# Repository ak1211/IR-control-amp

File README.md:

# IR-control-amp

## Overview
Infra Red remote control amplifier firmware on atmega328p

## Description
このソフトウエアはatmega328p使用  
赤外線リモコンコントロールヘッドホンアンプ基板Rev: A2.x用  
組込みファームウエアです。

## Requirements
Atmel Studio 7 (Version: 7.0.594 - )
© 2015 Atmel Corp.
All rights reserved.

## Compile and Link
Atmel Studio 7で[solution file](https://github.com/ak1211/IR-control-amp/blob/master/AudioAmpApplication/AudioAmpApplication.atsln)
を開いてコンパイル＆リンクを行ってください。

## License
[MIT](https://github.com/ak1211/IR-control-amp/blob/master/LICENSE)

## Author
[ak1211](https://github.com/ak1211/) - [blog](https://ak1211.com/index.php)

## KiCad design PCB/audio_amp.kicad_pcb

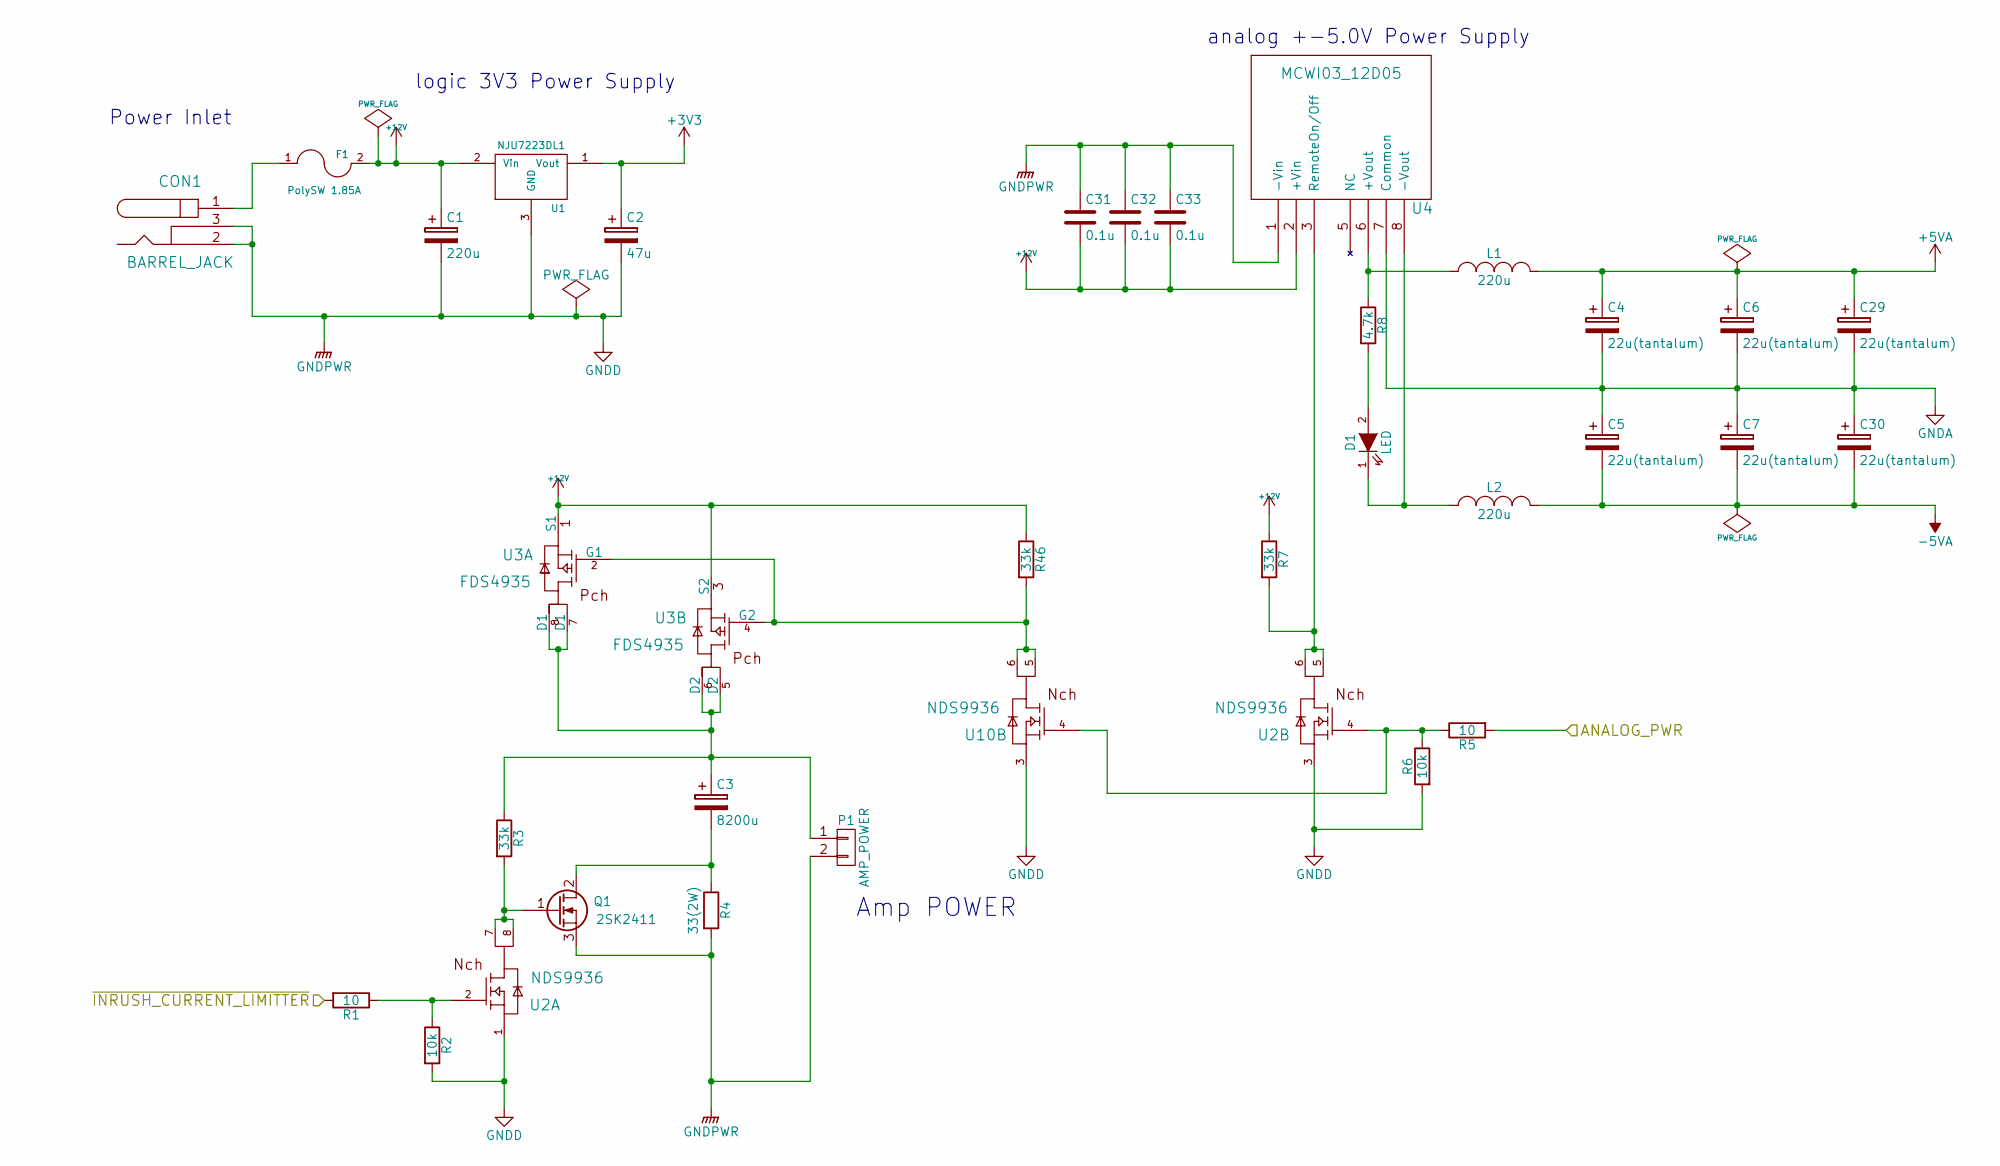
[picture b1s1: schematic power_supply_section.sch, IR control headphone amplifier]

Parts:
C1: 220u; c_elec_10x10.5
C2: 47u; c_elec_10x10.5
C3: 8200u; C_Radial_D18_L36_P7.5
C4, C5, C6, C7, C29, C30: 22u(tantalum); TantalC_SizeA_EIA-3216_HandSoldering
C31, C32, C33: 0.1u; C_0805_HandSoldering
CON1: BARREL_JACK
D1: LED; LED-0805
F1: PolySW 1.85A; Fuse_TE5_Littlefuse-395Series
L1, L2: 220u; Choke_SMD_10.4x10.4_H4.8
P1: AMP_POWER; Socket_MOLEX-KK-RM3-96mm_Lock_2pin_straight
Q1: 2SK2411; sot404
R1, R5: 10; R_0805_HandSoldering
R2, R6: 10k; R_0805_HandSoldering
R3, R7, R46: 33k; R_0805_HandSoldering
R4: 33(2W); Resistor_Horizontal_RM20mm
R8: 4.7k; R_0805_HandSoldering
U1: NJU7223DL1; sot428
U2, U10: NDS9936; SOIC-8_3.9x4.9mm_Pitch1.27mm
U3: FDS4935; SOIC-8_3.9x4.9mm_Pitch1.27mm
U4: MCWI03_12D05; MINMAX_MCWI03-12x

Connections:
+3V3: C2.1, U1.1 (Vout); also elsewhere on the board
+5VA: C4.1, C6.1, C29.1, L1.2; also elsewhere on the board
+12V: C1.1, C31.2, C32.2, C33.2, F1.2, R7.1, R46.1, U1.2 (Vin), U3.1 (S1), U3.3 (S2), U4.2 (+Vin); also elsewhere on the board
-5VA: C5.2, C7.2, C30.2, L2.2; also elsewhere on the board
/controller_section/ANALOG_PWR: R5.2; also elsewhere on the board
/controller_section/~INRUSH_CURRENT_LIMITTER: R1.2; also elsewhere on the board
GNDA: C4.2, C5.1, C6.2, C7.1, C29.2, C30.1, U4.7 (Common); also elsewhere on the board
GNDD: C1.2, C2.2, C31.1, C32.1, C33.1, CON1.2, CON1.3, P1.2, Q1.3 (S), R2.2, R4.2, R6.2, U1.3 (GND), U2.1, U2.3, U4.1 (-Vin), U10.3; also elsewhere on the board
unnamed: C3.1, P1.1, R3.1, U3.5 (D2), U3.6 (D2), U3.7 (D1), U3.8 (D1)
unnamed: C3.2, Q1.2 (D), R4.1
unnamed: CON1.1, F1.1
unnamed: D1.1 (K), L2.1, U4.8 (-Vout)
unnamed: D1.2 (A), R8.2
unnamed: L1.1, R8.1, U4.6 (+Vout)
unnamed: Q1.1 (G), R3.2, U2.7, U2.8
unnamed: R1.1, R2.1, U2.2
unnamed: R5.1, R6.1, U2.4, U10.4
unnamed: R7.2, U2.5, U2.6, U4.3 (RemoteOn/Off)
unnamed: R46.2, U3.2 (G1), U3.4 (G2), U10.5, U10.6

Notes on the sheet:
analog +-5.0V Power Supply
Power Inlet
logic 3V3 Power Supply
Amp POWER

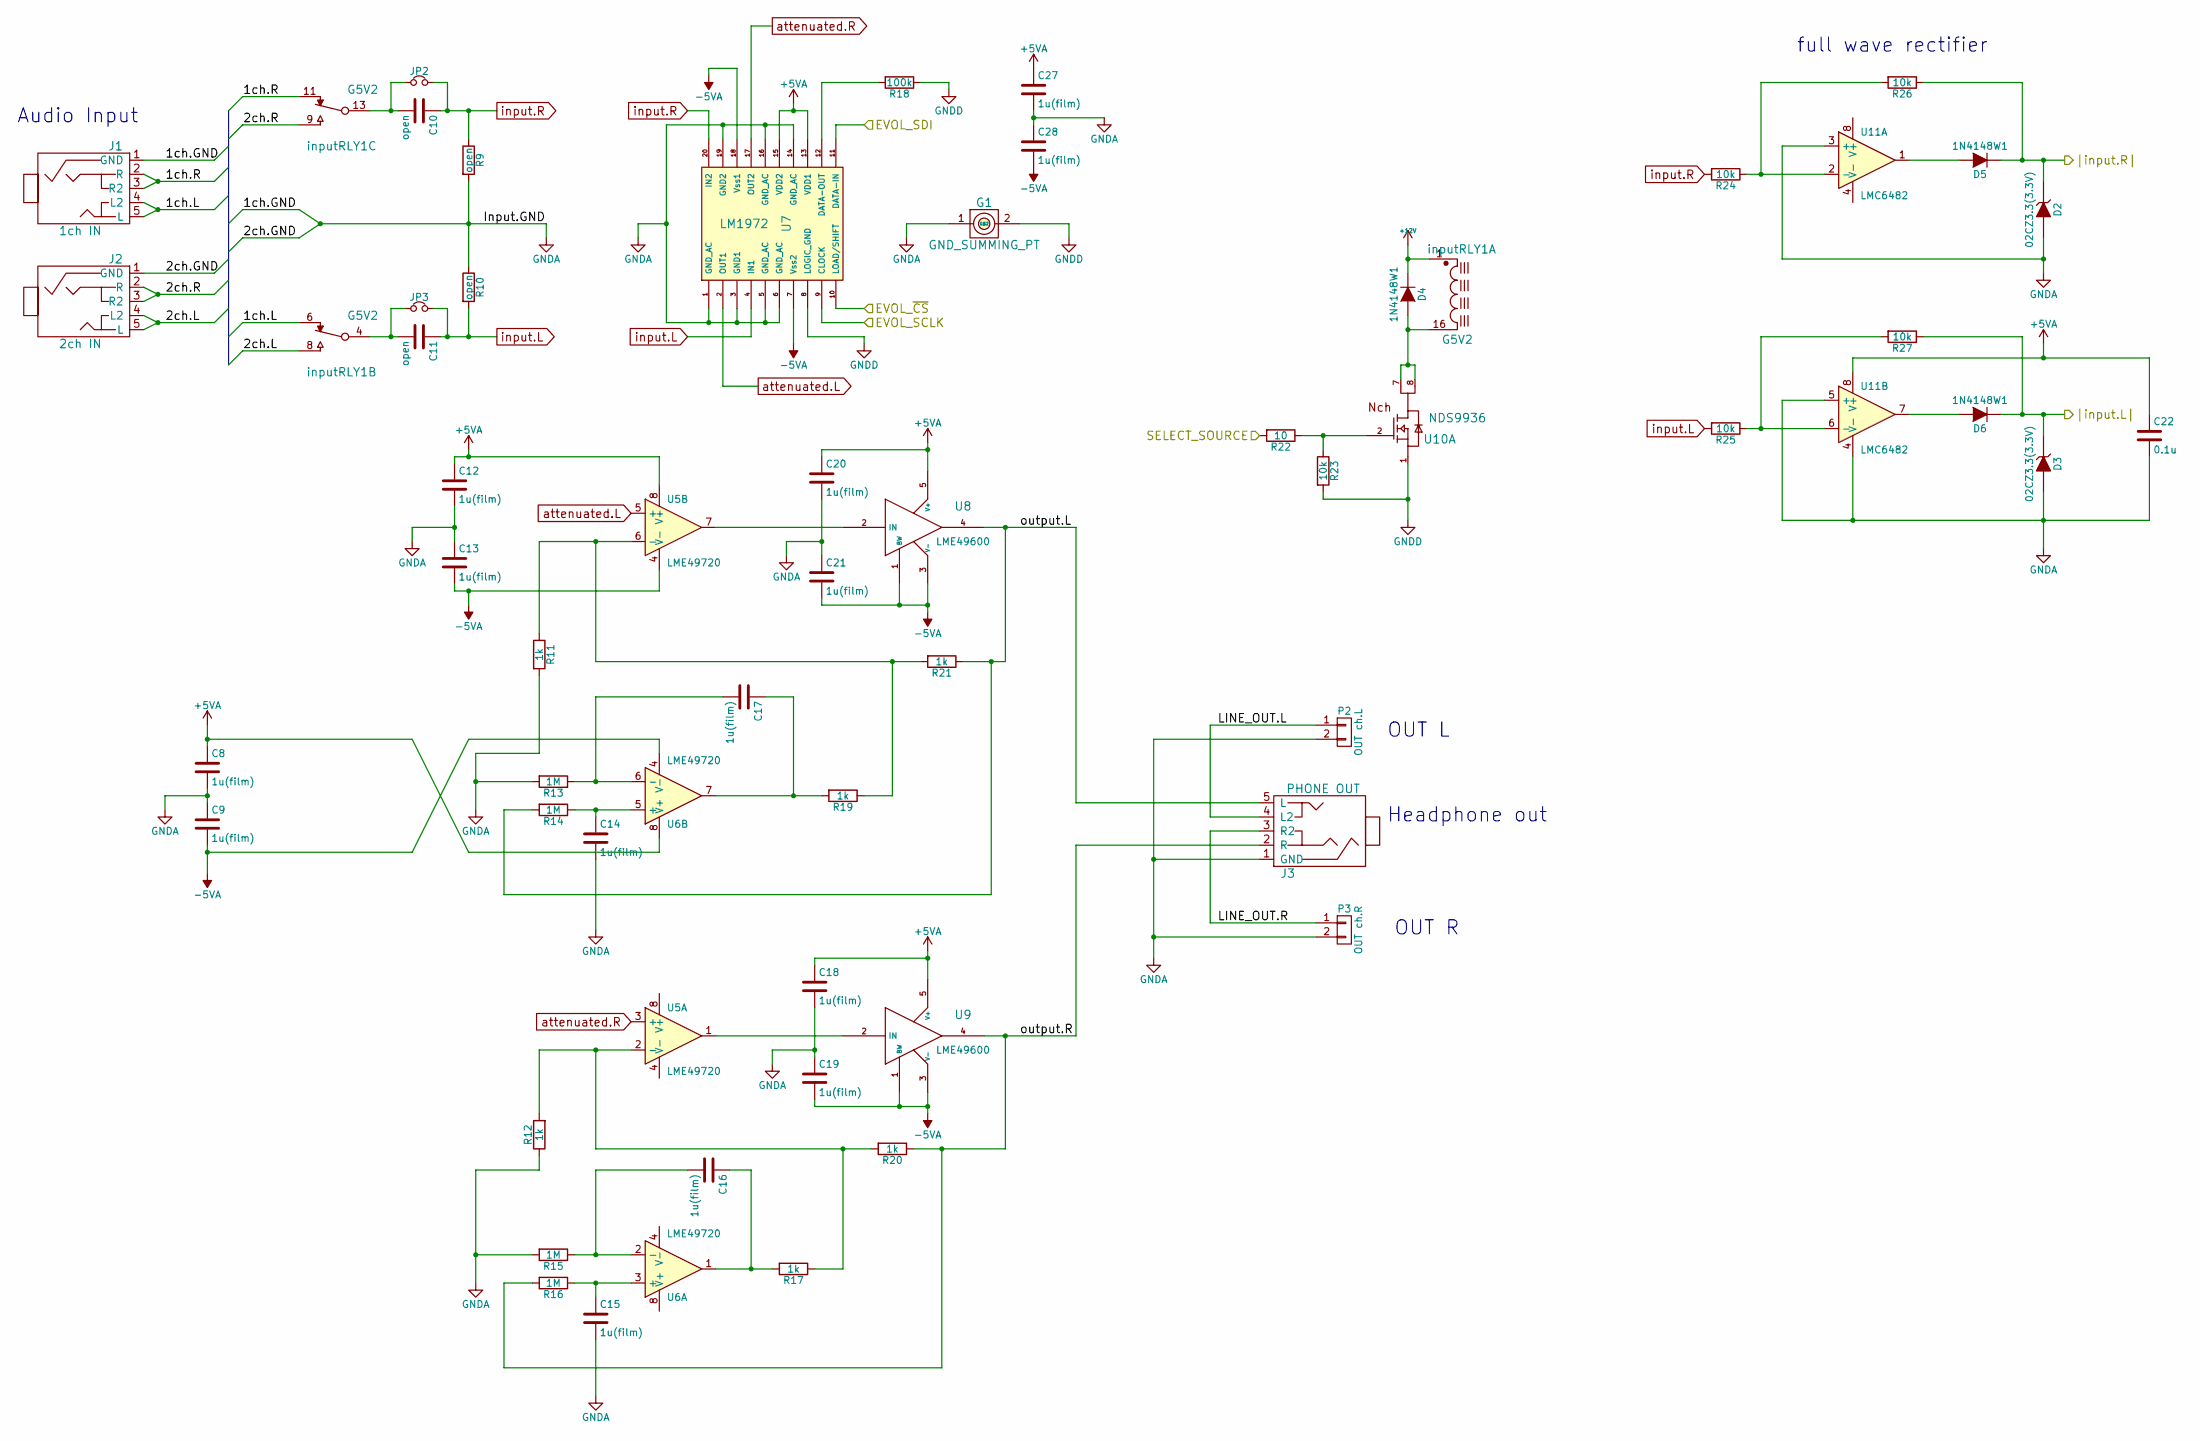
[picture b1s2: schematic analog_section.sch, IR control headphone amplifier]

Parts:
C8, C9, C12, C13, C14, C15, C16, C17, C18, C19, C20, C21, C27, C28: 1u(film); C_1206_HandSoldering
C10, C11: open; C_1206_HandSoldering
C22: 0.1u; C_0805_HandSoldering
D2, D3: 02CZ3.3(3.3V); SC-59
D4, D5, D6: 1N4148W1; SOD-123
G1: GND_SUMMING_PT
J1: 1ch IN; AJ-1780
J2: 2ch IN; AJ-1780
J3: PHONE OUT; AJ-1780
JP2, JP3: Jumper_NC_Small; GS2
P2: OUT ch.L; Socket_MOLEX-KK-RM2-54mm_Lock_2pin_straight
P3: OUT ch.R; Socket_MOLEX-KK-RM2-54mm_Lock_2pin_straight
R9, R10: open; R_0805_HandSoldering
R11, R12, R17, R19, R20, R21: 1k; R_0805_HandSoldering
R13, R14, R15, R16: 1M; R_0805_HandSoldering
R18: 100k; R_0805_HandSoldering
R22: 10; R_0805_HandSoldering
R23, R24, R25, R26, R27: 10k; R_0805_HandSoldering
U5, U6: LME49720
U7: LM1972; SOIC-20_7.5x12.8mm_Pitch1.27mm
U8, U9: LME49600
U10: NDS9936; SOIC-8_3.9x4.9mm_Pitch1.27mm
U11: LMC6482
inputRLY1: G5V2; G5V-2

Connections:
+5VA: C8.1, C12.1, C18.1, C20.1, C22.1, C27.1, U5.8 (V+), U6.8 (V+), U7.13 (VDD1), U7.15 (VDD2), U8.5 (V+), U9.5 (V+), U11.8 (V+); also elsewhere on the board
+12V: D4.1 (K), inputRLY1.1; also elsewhere on the board
-5VA: C9.2, C13.2, C19.2, C21.2, C28.2, U5.4 (V-), U6.4 (V-), U7.7 (Vss2), U7.18 (Vss1), U8.1 (BW), U8.3 (V-), U9.1 (BW), U9.3 (V-); also elsewhere on the board
/analog_section/1ch.L: J1.4 (L2), J1.5 (L), inputRLY1.6
/analog_section/1ch.R: J1.2 (R), J1.3 (R2), inputRLY1.11
/analog_section/2ch.L: J2.4 (L2), J2.5 (L), inputRLY1.8
/analog_section/2ch.R: J2.2 (R), J2.3 (R2), inputRLY1.9
/analog_section/EVOL_SCLK: U7.9 (CLOCK); also elsewhere on the board
/analog_section/EVOL_SDI: U7.11 (DATA-IN); also elsewhere on the board
/analog_section/EVOL_~CS: U7.10 (LOAD/SHIFT); also elsewhere on the board
/analog_section/LINE_OUT.L: J3.4 (L2), P2.1
/analog_section/LINE_OUT.R: J3.3 (R2), P3.1
/analog_section/SELECT_SOURCE: R22.2; also elsewhere on the board
/analog_section/output.L: J3.5 (L), R14.2, R21.1, U8.4
/analog_section/output.R: J3.2 (R), R16.2, R20.1, U9.4
/analog_section/|input.L|: D3.1 (K), D6.1 (K), R27.1; also elsewhere on the board
/analog_section/|input.R|: D2.1 (K), D5.1 (K), R26.1; also elsewhere on the board
GNDA: C8.2, C9.1, C12.2, C13.1, C14.2, C15.2, C18.2, C19.1, C20.2, C21.1, C22.2, C27.2, C28.1, D2.2 (A), D3.2 (A), G1.1 (G1), J1.1 (GND), J2.1 (GND), J3.1 (GND), P2.2, P3.2, R9.2, R10.1, R11.2, R12.1, R13.2, R15.2, U7.1 (GND_AC), U7.3 (GND1), U7.5 (GND_AC), U7.6 (GND_AC), U7.14 (GND_AC), U7.16 (GND_AC), U7.19 (GND2), U11.3 (+), U11.4 (V-), U11.5 (+); also elsewhere on the board
GNDD: G1.2 (G2), R18.1, R23.2, U7.8 (LOGIC_GND), U10.1; also elsewhere on the board
unnamed: C10.2, JP2.1, inputRLY1.13
unnamed: C11.2, JP3.1, inputRLY1.4
unnamed: C14.1, R14.1, U6.5 (+)
unnamed: C15.1, R16.1, U6.3 (+)
unnamed: C16.1, R17.2, U6.1
unnamed: C16.2, R15.1, U6.2 (-)
unnamed: C17.1, R19.2, U6.7
unnamed: C17.2, R13.1, U6.6 (-)
unnamed: D4.2 (A), U10.7, U10.8, inputRLY1.16
unnamed: D5.2 (A), U11.1
unnamed: D6.2 (A), U11.7
unnamed: R11.1, R19.1, R21.2, U5.6 (-)
unnamed: R12.2, R17.1, R20.2, U5.2 (-)
unnamed: R18.2, U7.12 (DATA-OUT)
unnamed: R22.1, R23.1, U10.2
unnamed: R24.1, R26.2, U11.2 (-)
unnamed: R25.1, R27.2, U11.6 (-)
unnamed: U5.1, U9.2 (IN)
unnamed: U5.7, U8.2 (IN)
attenuated.L: U5.5 (+), U7.2 (OUT1)
attenuated.R: U5.3 (+), U7.17 (OUT2)
input.L: C11.1, JP3.2, R10.2, R25.2, U7.4 (IN1)
input.R: C10.1, JP2.2, R9.1, R24.2, U7.20 (IN2)

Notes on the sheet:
OUT R
Audio Input
Headphone out
full wave rectifier
OUT L

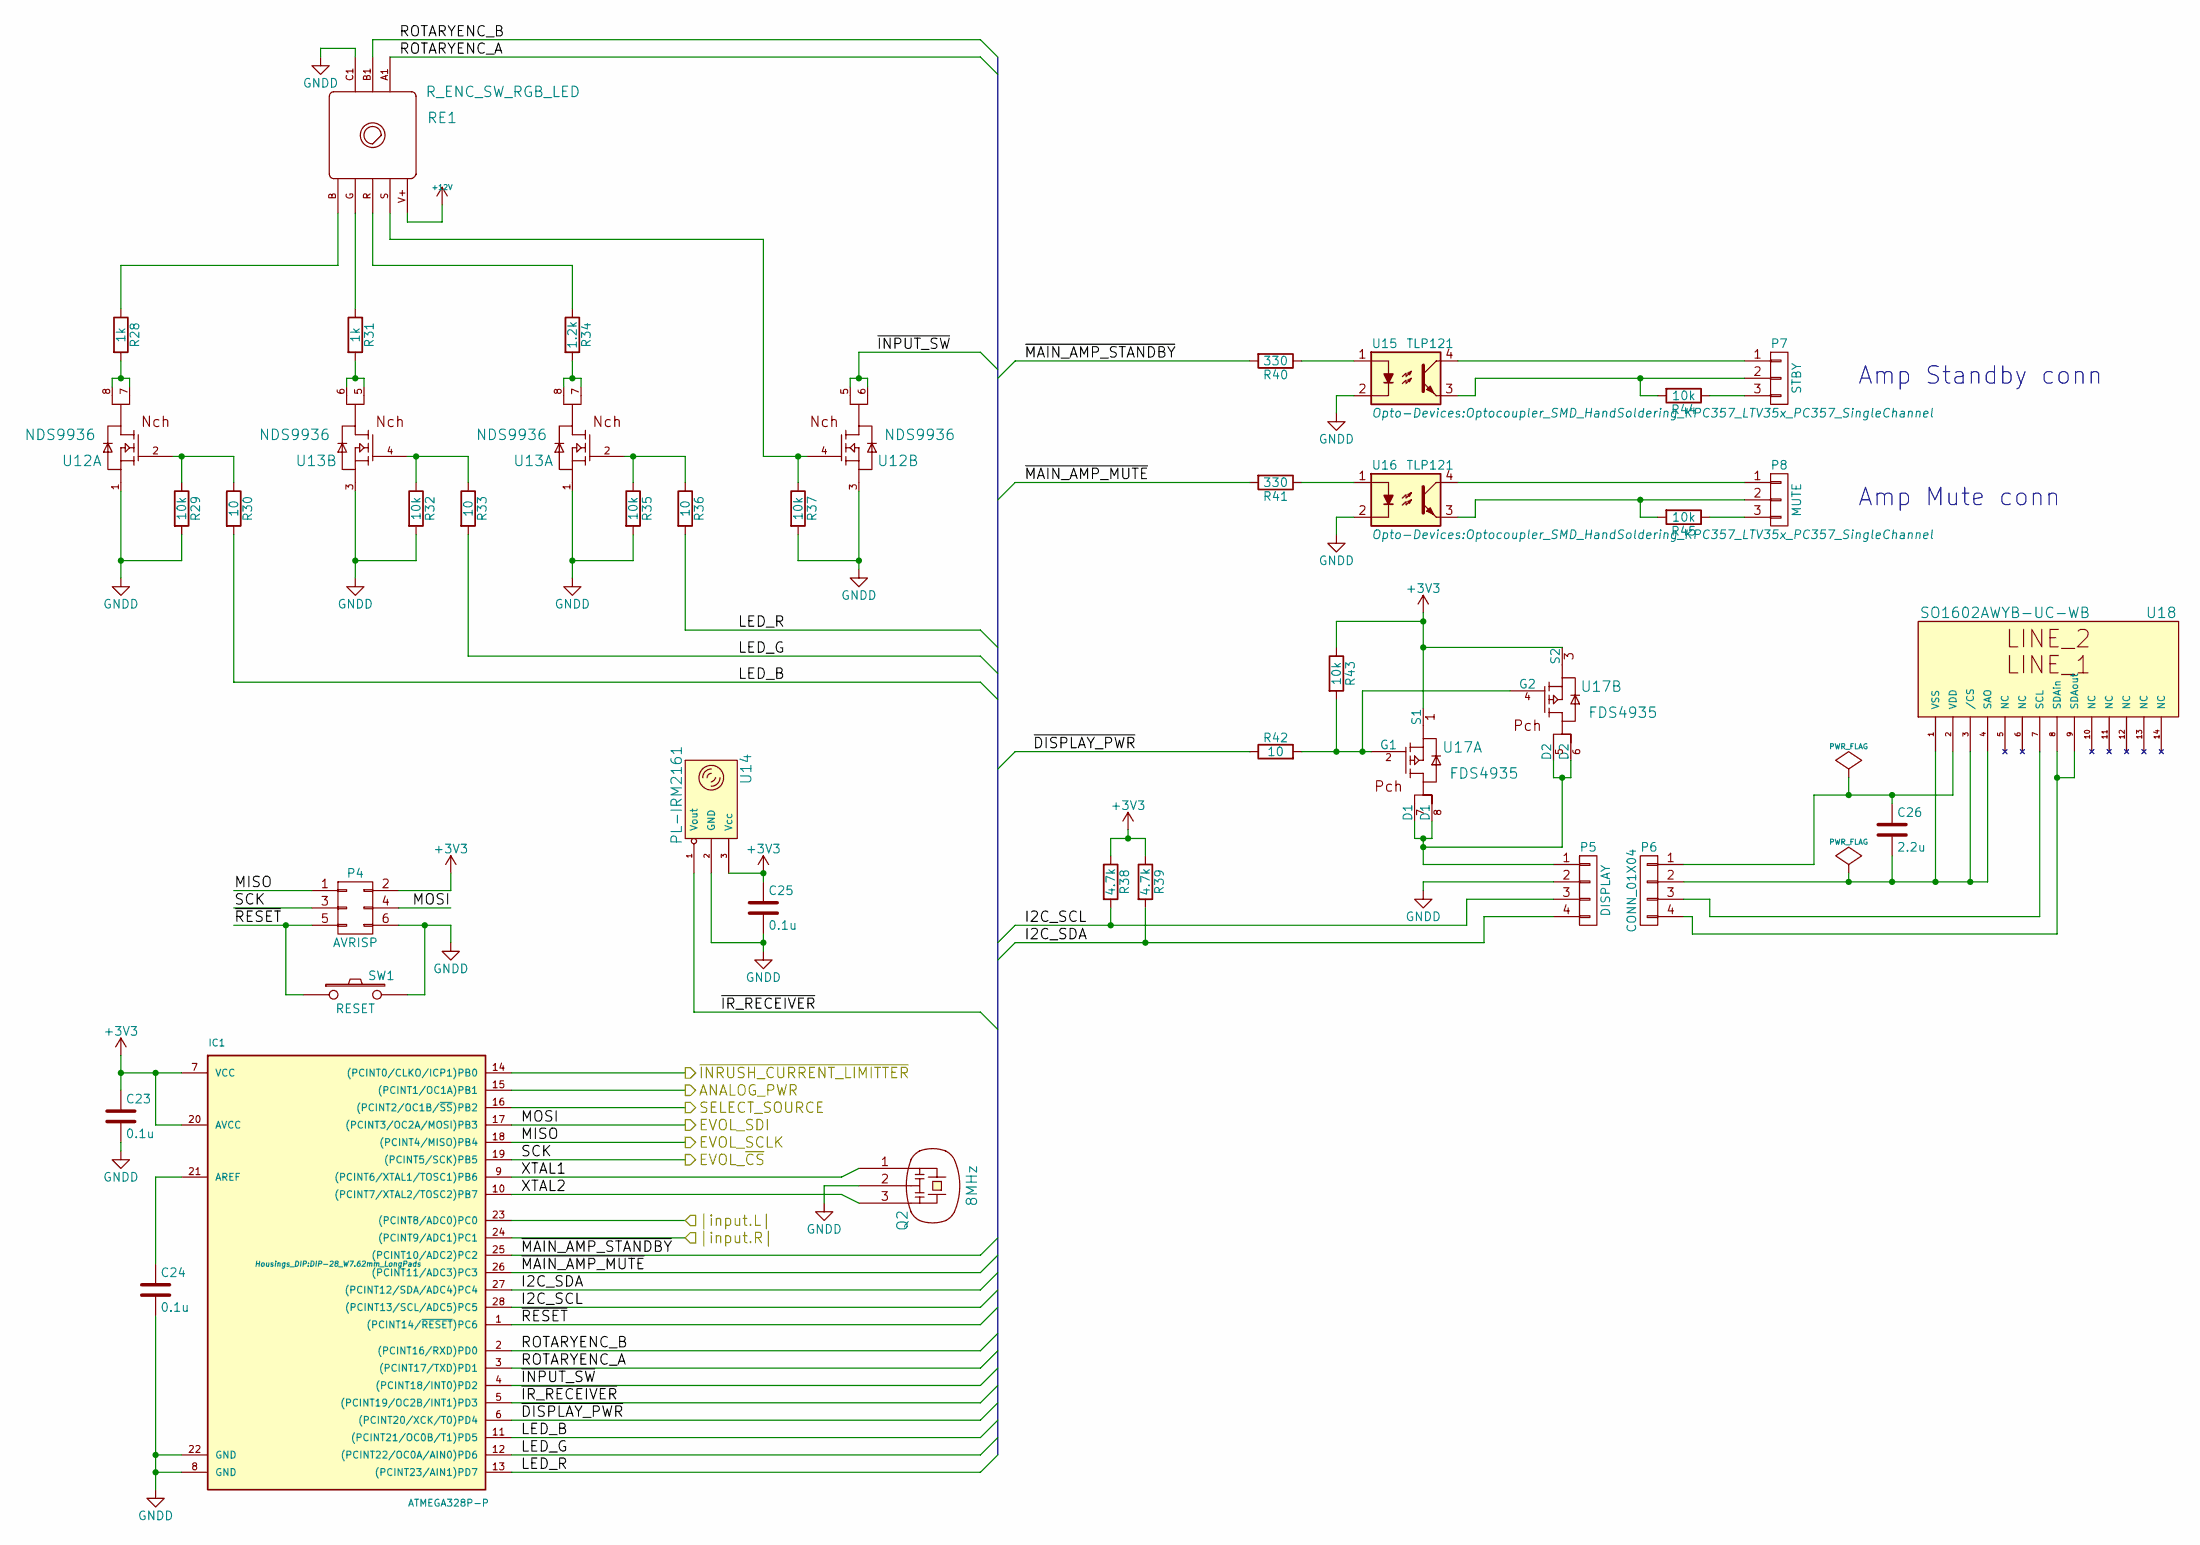
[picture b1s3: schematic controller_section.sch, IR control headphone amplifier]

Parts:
C23, C24, C25: 0.1u; C_0805_HandSoldering
C26: 2.2u; C_1206_HandSoldering
IC1: ATMEGA328P-P; DIP-28_W7.62mm_LongPads
P4: AVRISP; AVRISP_Angled
P5: DISPLAY; Socket_MOLEX-KK-RM2-54mm_Lock_4pin_straight
P6: CONN_01X04; Socket_MOLEX-KK-RM2-54mm_Lock_4pin_straight
P7: STBY; Socket_MOLEX-KK-RM2-54mm_Lock_3pin_straight
P8: MUTE; Socket_MOLEX-KK-RM2-54mm_Lock_3pin_straight
Q2: 8MHz; CERALOCK
R28, R31: 1k; R_0805_HandSoldering
R29, R32, R35, R37, R43, R44, R45: 10k; R_0805_HandSoldering
R30, R33, R36, R42: 10; R_0805_HandSoldering
R34: 1.2k; R_0805_HandSoldering
R38, R39: 4.7k; R_0805_HandSoldering
R40, R41: 330; R_0805_HandSoldering
RE1: R_ENC_SW_RGB_LED; EC12PLRGBSDHF
SW1: RESET; ALPS_TACT_SW_SKHHL
U12, U13: NDS9936; SOIC-8_3.9x4.9mm_Pitch1.27mm
U14: PL-IRM2161
U15, U16: TLP121; Optocoupler_SMD_HandSoldering_KPC357_LTV35x_PC357_SingleCha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
U17: FDS4935; SOIC-8_3.9x4.9mm_Pitch1.27mm
U18: SO1602AWYB-UC-WB; WC1602A

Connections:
+3V3: C23.1, C25.1, IC1.7 (VCC), IC1.20 (AVCC), P4.2, R38.1, R39.1, R43.1, U14.3 (Vcc), U17.1 (S1), U17.3 (S2); also elsewhere on the board
+12V: RE1.V+; also elsewhere on the board
/analog_section/EVOL_SCLK: IC1.18 ((PCINT4/MISO)PB4), P4.1; also elsewhere on the board
/analog_section/EVOL_SDI: IC1.17 ((PCINT3/OC2A/MOSI)PB3), P4.4; also elsewhere on the board
/analog_section/EVOL_~CS: IC1.19 ((PCINT5/SCK)PB5), P4.3; also elsewhere on the board
/analog_section/SELECT_SOURCE: IC1.16 ((PCINT2/OC1B/~SS~)PB2); also elsewhere on the board
/analog_section/|input.L|: IC1.23 ((PCINT8/ADC0)PC0); also elsewhere on the board
/analog_section/|input.R|: IC1.24 ((PCINT9/ADC1)PC1); also elsewhere on the board
/controller_section/ANALOG_PWR: IC1.15 ((PCINT1/OC1A)PB1); also elsewhere on the board
/controller_section/I2C_SCL: IC1.28 ((PCINT13/SCL/ADC5)PC5), P5.3, R38.2
/controller_section/I2C_SDA: IC1.27 ((PCINT12/SDA/ADC4)PC4), P5.4, R39.2
/controller_section/LED_B: IC1.11 ((PCINT21/OC0B/T1)PD5), R30.2
/controller_section/LED_G: IC1.12 ((PCINT22/OC0A/AIN0)PD6), R33.2
/controller_section/LED_R: IC1.13 ((PCINT23/AIN1)PD7), R36.2
/controller_section/ROTARYENC_A: IC1.3 ((PCINT17/TXD)PD1), RE1.A1
/controller_section/ROTARYENC_B: IC1.2 ((PCINT16/RXD)PD0), RE1.B1
/controller_section/XTAL1: IC1.9 ((PCINT6/XTAL1/TOSC1)PB6), Q2.1
/controller_section/XTAL2: IC1.10 ((PCINT7/XTAL2/TOSC2)PB7), Q2.3
/controller_section/~DISPLAY_PWR: IC1.6 ((PCINT20/XCK/T0)PD4), R42.1
/controller_section/~INPUT_SW: IC1.4 ((PCINT18/INT0)PD2), U12.5, U12.6
/controller_section/~INRUSH_CURRENT_LIMITTER: IC1.14 ((PCINT0/CLKO/ICP1)PB0); also elsewhere on the board
/controller_section/~IR_RECEIVER: IC1.5 ((PCINT19/OC2B/INT1)PD3), U14.1 (Vout)
/controller_section/~MAIN_AMP_MUTE: IC1.26 ((PCINT11/ADC3)PC3), R41.2
/controller_section/~MAIN_AMP_STANDBY: IC1.25 ((PCINT10/ADC2)PC2), R40.2
/controller_section/~RESET: IC1.1 ((PCINT14/~RESET~)PC6), P4.5, SW1.1
GNDD: C23.2, C24.2, C25.2, IC1.8 (GND), IC1.22 (GND), P4.6, P5.2, Q2.2, R29.2, R32.2, R35.2, R37.2, RE1.C1, SW1.2, U12.1, U12.3, U13.1, U13.3, U14.2 (GND), U15.2, U16.2; also elsewhere on the board
unnamed: C24.1, IC1.21 (AREF)
unnamed: C26.1, P6.1, U18.2 (VDD)
unnamed: C26.2, P6.2, U18.1 (VSS), U18.3 (/CS), U18.4 (SAO)
unnamed: P5.1, U17.5 (D2), U17.6 (D2), U17.7 (D1), U17.8 (D1)
unnamed: P6.3, U18.7 (SCL)
unnamed: P6.4, U18.8 (SDAin), U18.9 (SDAout)
unnamed: P7.1, U15.4
unnamed: P7.2, R44.2, U15.3
unnamed: P7.3, R44.1
unnamed: P8.1, U16.4
unnamed: P8.2, R45.2, U16.3
unnamed: P8.3, R45.1
unnamed: R28.1, RE1.B
unnamed: R28.2, U12.7, U12.8
unnamed: R29.1, R30.1, U12.2
unnamed: R31.1, RE1.G
unnamed: R31.2, U13.5, U13.6
unnamed: R32.1, R33.1, U13.4
unnamed: R34.1, RE1.R
unnamed: R34.2, U13.7, U13.8
unnamed: R35.1, R36.1, U13.2
unnamed: R37.1, RE1.S, U12.4
unnamed: R40.1, U15.1
unnamed: R41.1, U16.1
unnamed: R42.2, R43.2, U17.2 (G1), U17.4 (G2)

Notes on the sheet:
Amp Standby conn
Amp Mute conn

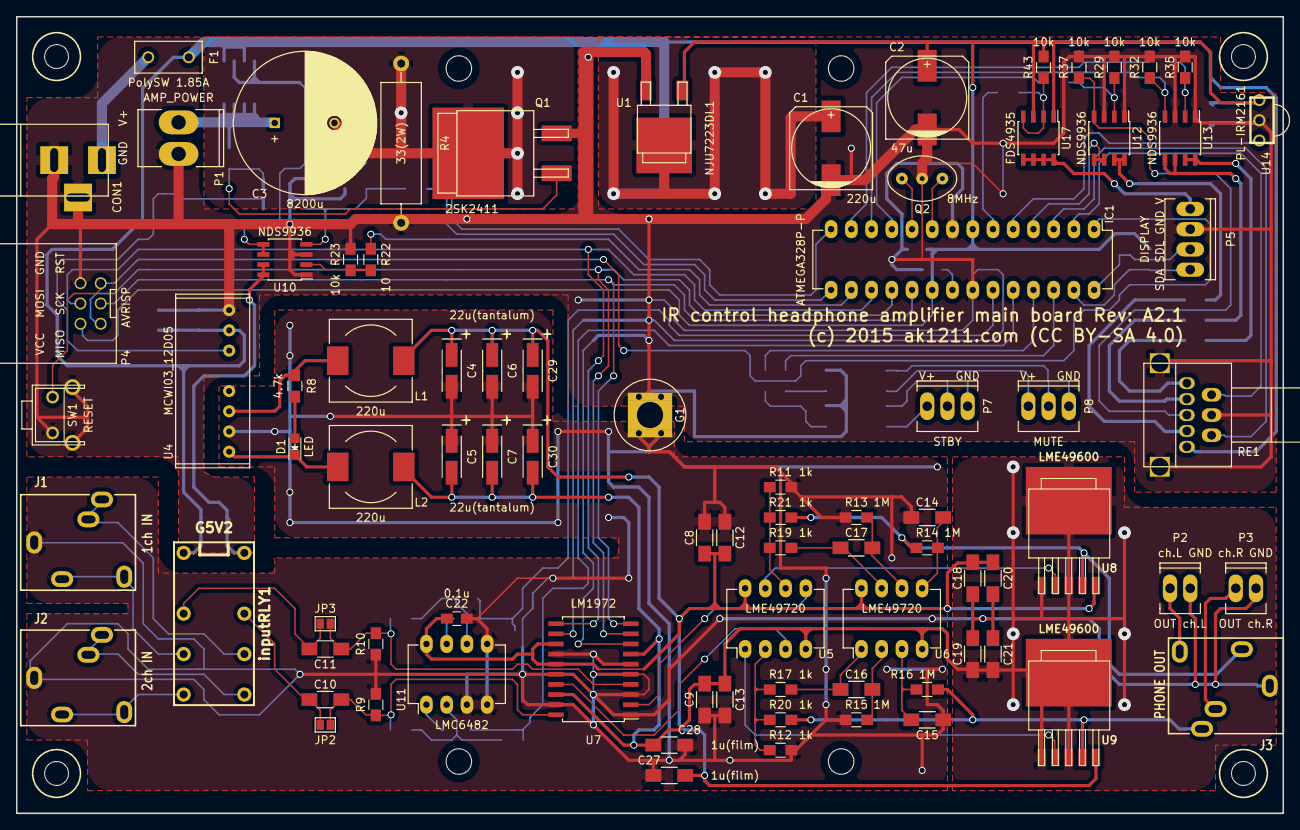
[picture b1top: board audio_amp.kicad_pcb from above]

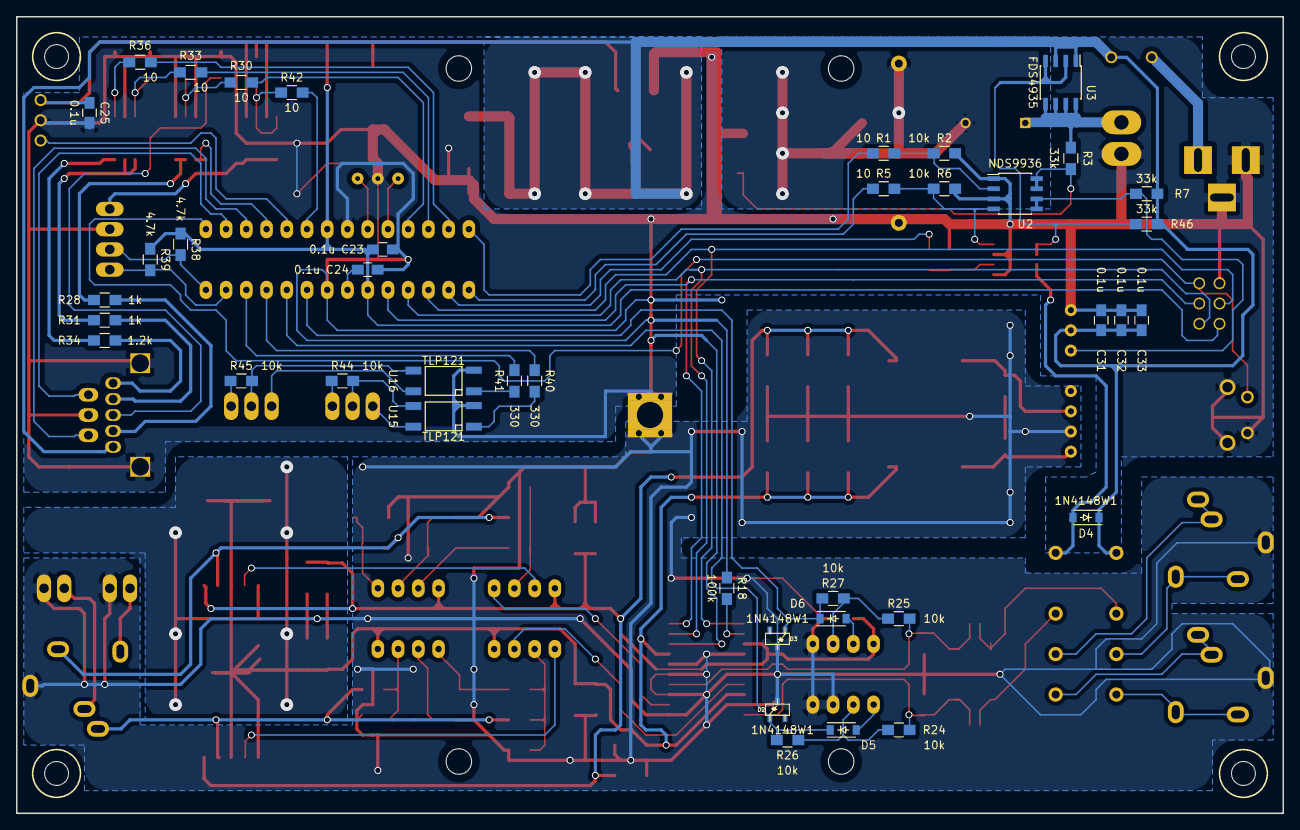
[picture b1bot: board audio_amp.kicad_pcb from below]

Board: 2 copper layers, 159.0 x 100.0 mm, 128 parts (40 on the bottom side), 92 nets.

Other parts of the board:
hole_m3, hole_m3#2, hole_m3#3, hole_m3#4: P***; hole_m3

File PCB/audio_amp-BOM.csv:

Reference, Value, Footprint, Datasheet
L1,220u,Choke_SMD:Choke_SMD_10.4x10.4_H4.8,
L2,220u,Choke_SMD:Choke_SMD_10.4x10.4_H4.8,
U1,NJU7223DL1,Transistors_SMD:sot428,
F1,PolySW 1.85A,Fuse_Holders_and_Fuses:Fuse_TE5_Littlefuse-395Series,
CON1,BARREL_JACK,Connect:BARREL_JACK,
U3,FDS4935,Housings_SOIC:SOIC-8_3.9x4.9mm_Pitch1.27mm,
U2,NDS9936,Housings_SOIC:SOIC-8_3.9x4.9mm_Pitch1.27mm,
U4,MCWI03_12D05,mylib:MINMAX_MCWI03-12x,
Q1,2SK2411,Transistors_SMD:sot404,
C3,8200u,Capacitors_ThroughHole:C_Radial_D18_L36_P7.5,
C1,220u,Capacitors_SMD:c_elec_10x10.5,
C2,47u,Capacitors_SMD:c_elec_10x10.5,
C4,22u(tantalum),Capacitors_Tantalum_SMD:TantalC_SizeA_EIA-3216_HandSoldering,
C5,22u(tantalum),Capacitors_Tantalum_SMD:TantalC_SizeA_EIA-3216_HandSoldering,
C6,22u(tantalum),Capacitors_Tantalum_SMD:TantalC_SizeA_EIA-3216_HandSoldering,
C7,22u(tantalum),Capacitors_Tantalum_SMD:TantalC_SizeA_EIA-3216_HandSoldering,
D1,LED,LEDs:LED-0805,
P1,AMP_POWER,Sockets_MOLEX_KK-System:Socket_MOLEX-KK-RM3-96mm_Lock_2pin_straight,
R1,10,Resistors_SMD:R_0805_HandSoldering,
R2,10k,Resistors_SMD:R_0805_HandSoldering,
R3,33k,Resistors_SMD:R_0805_HandSoldering,
R4,33(2W),Resistors_ThroughHole:Resistor_Horizontal_RM20mm,
R5,10,Resistors_SMD:R_0805_HandSoldering,
R6,10k,Resistors_SMD:R_0805_HandSoldering,
R7,33k,Resistors_SMD:R_0805_HandSoldering,
R8,4.7k,Resistors_SMD:R_0805_HandSoldering,
C30,22u(tantalum),Capacitors_Tantalum_SMD:TantalC_SizeA_EIA-3216_HandSoldering,
C29,22u(tantalum),Capacitors_Tantalum_SMD:TantalC_SizeA_EIA-3216_HandSoldering,
C32,0.1u,Capacitors_SMD:C_0805_HandSoldering,
C31,0.1u,Capacitors_SMD:C_0805_HandSoldering,
C33,0.1u,Capacitors_SMD:C_0805_HandSoldering,
U10,NDS9936,Housings_SOIC:SOIC-8_3.9x4.9mm_Pitch1.27mm,
R46,33k,Resistors_SMD:R_0805_HandSoldering,
U8,LME49600,mylib:LME49600,
J3,PHONE OUT,toragi_201305:AJ-1780,
J1,1ch IN,toragi_201305:AJ-1780,
J2,2ch IN,toragi_201305:AJ-1780,
U7,LM1972,Housings_SOIC:SOIC-20_7.5x12.8mm_Pitch1.27mm,
C22,0.1u,Capacitors_SMD:C_0805_HandSoldering,
C15,1u(film),Capacitors_SMD:C_1206_HandSoldering,
C16,1u(film),Capacitors_SMD:C_1206_HandSoldering,
U9,LME49600,mylib:LME49600,
C18,1u(film),Capacitors_SMD:C_1206_HandSoldering,
C19,1u(film),Capacitors_SMD:C_1206_HandSoldering,
C14,1u(film),Capacitors_SMD:C_1206_HandSoldering,
C8,1u(film),Capacitors_SMD:C_1206_HandSoldering,
C9,1u(film),Capacitors_SMD:C_1206_HandSoldering,
C17,1u(film),Capacitors_SMD:C_1206_HandSoldering,
C12,1u(film),Capacitors_SMD:C_1206_HandSoldering,
C13,1u(film),Capacitors_SMD:C_1206_HandSoldering,
C20,1u(film),Capacitors_SMD:C_1206_HandSoldering,
C21,1u(film),Capacitors_SMD:C_1206_HandSoldering,
G1,GND_SUMMING_PT,mylib:GND_SUMMING_PT,
C11,open,Capacitors_SMD:C_1206_HandSoldering,
C10,open,Capacitors_SMD:C_1206_HandSoldering,
D2,02CZ3.3(3.3V),mylib_legacy:SC-59,
D3,02CZ3.3(3.3V),mylib_legacy:SC-59,
P2,OUT ch.L,Sockets_MOLEX_KK-System:Socket_MOLEX-KK-RM2-54mm_Lock_2pin_straight,
P3,OUT ch.R,Sockets_MOLEX_KK-System:Socket_MOLEX-KK-RM2-54mm_Lock_2pin_straight,
R9,open,Resistors_SMD:R_0805_HandSoldering,
R10,open,Resistors_SMD:R_0805_HandSoldering,
R18,100k,Resistors_SMD:R_0805_HandSoldering,
R22,10,Resistors_SMD:R_0805_HandSoldering,
R23,10k,Resistors_SMD:R_0805_HandSoldering,
R24,10k,Resistors_SMD:R_0805_HandSoldering,
R26,10k,Resistors_SMD:R_0805_HandSoldering,
R25,10k,Resistors_SMD:R_0805_HandSoldering,
R27,10k,Resistors_SMD:R_0805_HandSoldering,
R11,1k,Resistors_SMD:R_0805_HandSoldering,
R21,1k,Resistors_SMD:R_0805_HandSoldering,
R19,1k,Resistors_SMD:R_0805_HandSoldering,
R13,1M,Resistors_SMD:R_0805_HandSoldering,
R14,1M,Resistors_SMD:R_0805_HandSoldering,
R20,1k,Resistors_SMD:R_0805_HandSoldering,
R17,1k,Resistors_SMD:R_0805_HandSoldering,
R12,1k,Resistors_SMD:R_0805_HandSoldering,
R15,1M,Resistors_SMD:R_0805_HandSoldering,
R16,1M,Resistors_SMD:R_0805_HandSoldering,
D4,1N4148W1,Diodes_SMD:SOD-123,
D5,1N4148W1,Diodes_SMD:SOD-123,
D6,1N4148W1,Diodes_SMD:SOD-123,
inputRLY1,G5V2,mylib:G5V-2,
C27,1u(film),Capacitors_SMD:C_1206_HandSoldering,
C28,1u(film),Capacitors_SMD:C_1206_HandSoldering,
JP2,Jumper_NC_Small,Connect:GS2,
JP3,Jumper_NC_Small,Connect:GS2,
U11,LMC6482,,
U5,LME49720,,
U6,LME49720,,
Q2,8MHz,mylib:CERALOCK,
U14,PL-IRM2161,mylib:PL-IRM2161,
U18,SO1602AWYB-UC-WB,Display:WC1602A,
RE1,R_ENC_SW_RGB_LED,mylib:EC12PLRGBSDHF,
U13,NDS9936,Housings_SOIC:SOIC-8_3.9x4.9mm_Pitch1.27mm,
U12,NDS9936,Housings_SOIC:SOIC-8_3.9x4.9mm_Pitch1.27mm,
U17,FDS4935,Housings_SOIC:SOIC-8_3.9x4.9mm_Pitch1.27mm,
C23,0.1u,Capacitors_SMD:C_0805_HandSoldering,
C24,0.1u,Capacitors_SMD:C_0805_HandSoldering,
C26,2.2u,Capacitors_SMD:C_1206_HandSoldering,
U15,TLP121,Opto-Devices:Optocoupler_SMD_HandSoldering_KPC357_LTV35x_PC357_SingleChannel,
U16,TLP121,Opto-Devices:Optocoupler_SMD_HandSoldering_KPC357_LTV35x_PC357_SingleChannel,
IC1,ATMEGA328P-P,Housings_DIP:DIP-28_W7.62mm_LongPads,
P4,AVRISP,mylib:AVRISP_Angled,
SW1,RESET,mylib:ALPS_TACT_SW_SKHHL,
P7,STBY,Sockets_MOLEX_KK-System:Socket_MOLEX-KK-RM2-54mm_Lock_3pin_straight,
P8,MUTE,Sockets_MOLEX_KK-System:Socket_MOLEX-KK-RM2-54mm_Lock_3pin_straight,
P5,DISPLAY,Sockets_MOLEX_KK-System:Socket_MOLEX-KK-RM2-54mm_Lock_4pin_straight,
P6,CONN_01X04,Sockets_MOLEX_KK-System:Socket_MOLEX-KK-RM2-54mm_Lock_4pin_straight,
R28,1k,Resistors_SMD:R_0805_HandSoldering,
R31,1k,Resistors_SMD:R_0805_HandSoldering,
R34,1.2k,Resistors_SMD:R_0805_HandSoldering,
R29,10k,Resistors_SMD:R_0805_HandSoldering,
R30,10,Resistors_SMD:R_0805_HandSoldering,
R32,10k,Resistors_SMD:R_0805_HandSoldering,
R33,10,Resistors_SMD:R_0805_HandSoldering,
R35,10k,Resistors_SMD:R_0805_HandSoldering,
R36,10,Resistors_SMD:R_0805_HandSoldering,
R37,10k,Resistors_SMD:R_0805_HandSoldering,
R40,330,Resistors_SMD:R_0805_HandSoldering,
R41,330,Resistors_SMD:R_0805_HandSoldering,
R44,10k,Resistors_SMD:R_0805_HandSoldering,
R45,10k,Resistors_SMD:R_0805_HandSoldering,
R43,10k,Resistors_SMD:R_0805_HandSoldering,
R42,10,Resistors_SMD:R_0805_HandSoldering,
R38,4.7k,Resistors_SMD:R_0805_HandSoldering,
R39,4.7k,Resistors_SMD:R_0805_HandSoldering,
C25,0.1u,Capacitors_SMD:C_0805_HandSoldering,

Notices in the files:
PCB/analog_section.sch:
Copyright 2015 ak1211.com (CC BY-SA 4.0)
PCB/audio_amp.kicad_pcb:
(c) 2015 ak1211.com (CC BY-SA 4.0)
